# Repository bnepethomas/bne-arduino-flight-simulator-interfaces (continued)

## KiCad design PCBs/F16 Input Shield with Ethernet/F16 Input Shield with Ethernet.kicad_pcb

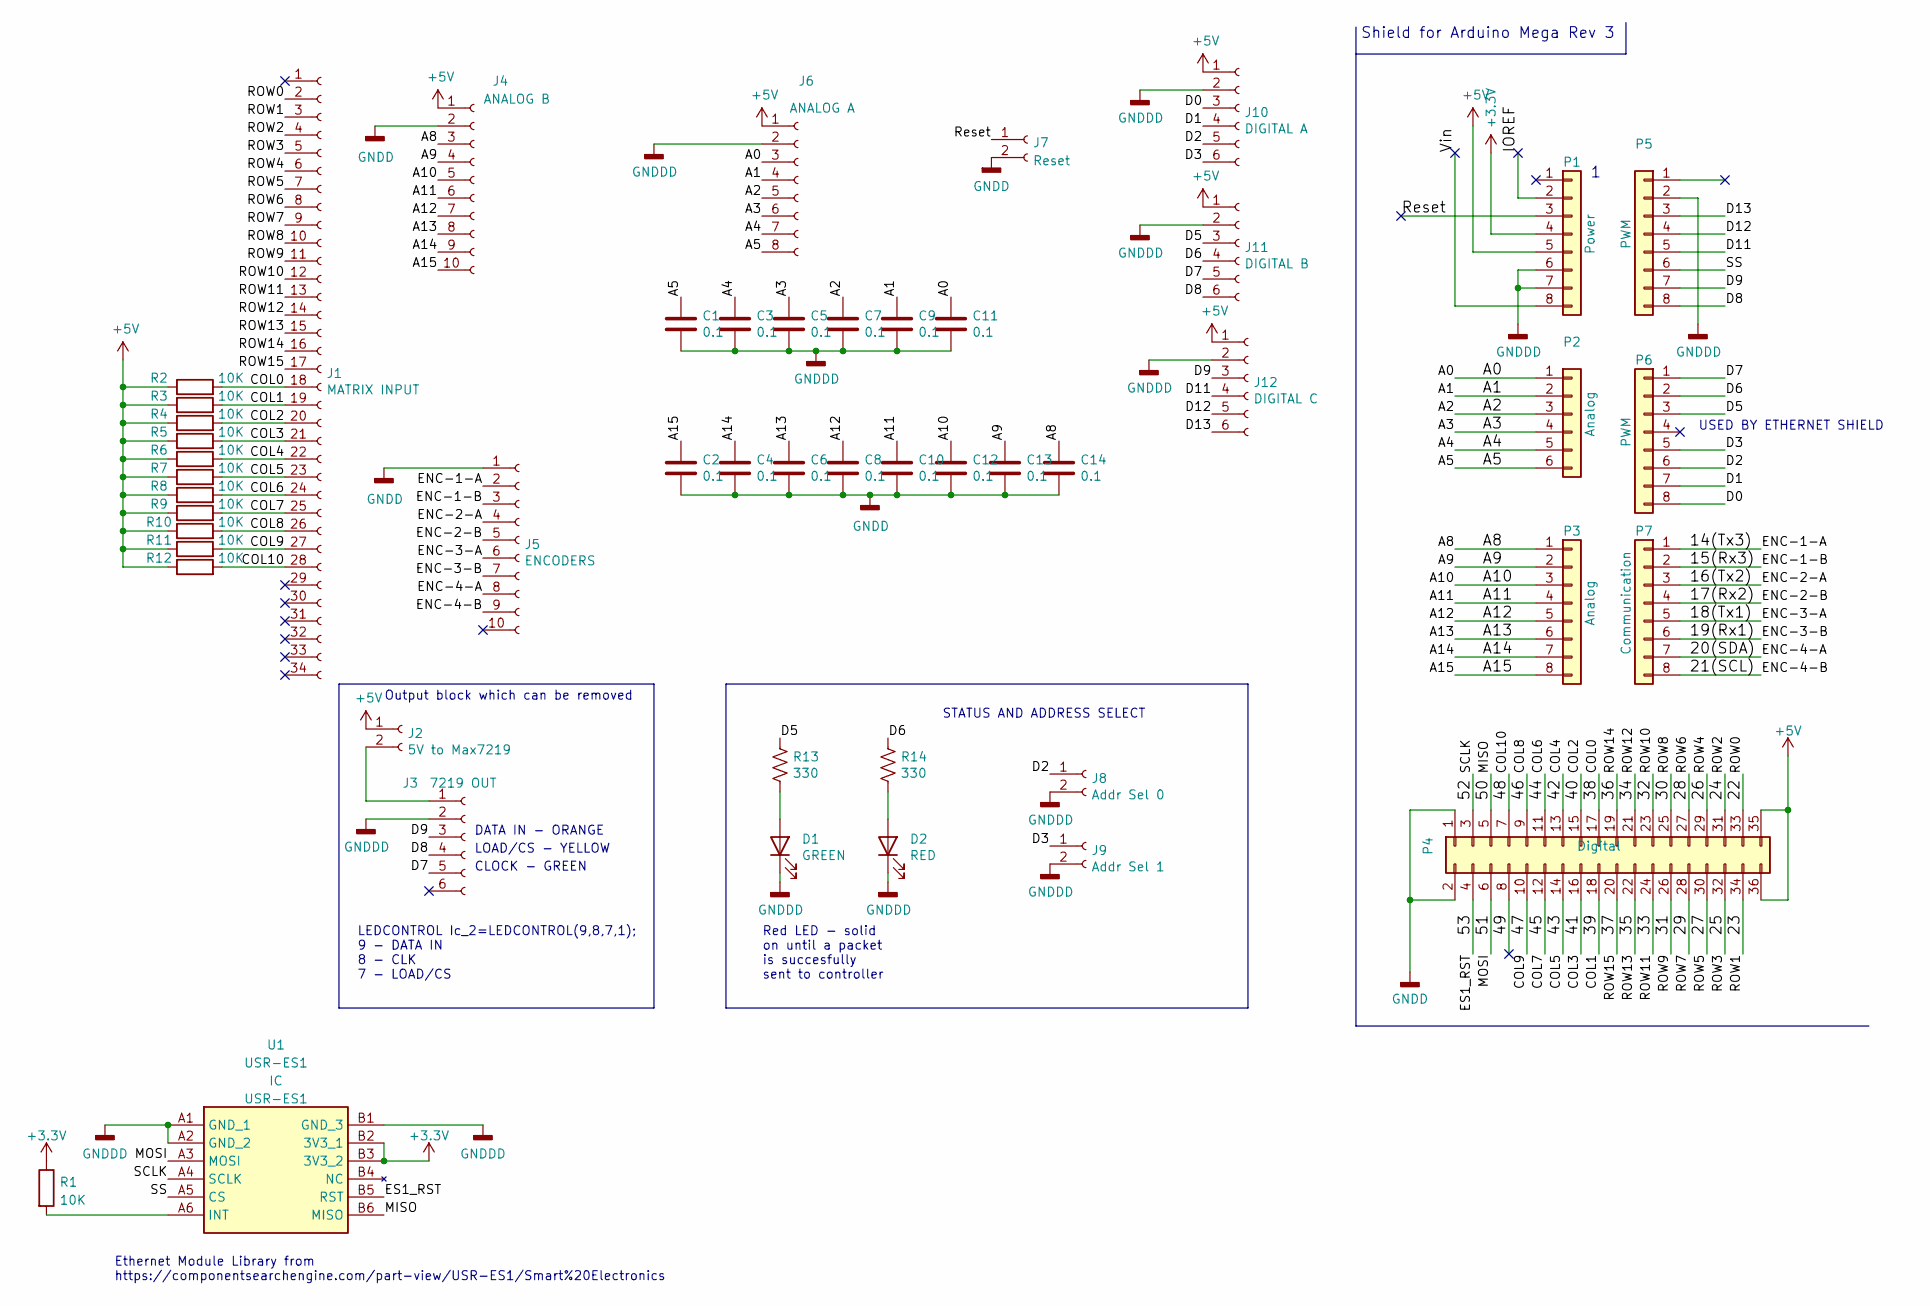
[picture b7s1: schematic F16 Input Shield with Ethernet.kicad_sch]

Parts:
C1, C2, C3, C4, C5, C6, C7, C8, C9, C10, C11, C12, C13, C14: 0.1; C_Disc_D6.0mm_W2.5mm_P5.00mm
D1: GREEN; LED_D3.0mm
D2: RED; LED_D3.0mm
J1: MATRIX INPUT; IDC-Header_2x17_P2.54mm_Vertical
J2: 5V to Max7219; Molex_1x02_P2.54mm_Vertical
J3: 7219 OUT; Molex_1x06_P2.54mm_Vertical
J4: ANALOG B; Molex_1x10_P2.54mm_Vertical
J5: ENCODERS; Molex_1x10_P2.54mm_Vertical
J6: ANALOG A; Molex_1x08_P2.54mm_Vertical
J7: Reset; PinHeader_1x02_P2.54mm_Vertical
J8: Addr Sel 0; PinHeader_1x02_P2.54mm_Vertical
J9: Addr Sel 1; PinHeader_1x02_P2.54mm_Vertical
J10: DIGITAL A; Molex_1x06_P2.54mm_Vertical
J11: DIGITAL B; Molex_1x06_P2.54mm_Vertical
J12: DIGITAL C; Molex_1x06_P2.54mm_Vertical
P1: Power; Socket_Strip_Arduino_1x08
P2: Analog; PinHeader_1x06_P2.54mm_Vertical
P3: Analog; Socket_Strip_Arduino_1x08
P4: Digital; Socket_Strip_Arduino_2x18
P5, P6: PWM; Socket_Strip_Arduino_1x08
P7: Communication; Socket_Strip_Arduino_1x08
R1, R2, R3, R4, R5, R6, R7, R8, R9, R10, R11, R12: 10K; PT_R_Axial_DIN0204_L3.6mm_D1.6mm_P2.54mm_Vertical
R13, R14: 330; PT_R_Axial_DIN0204_L3.6mm_D1.6mm_P2.54mm_Vertical
U1: USR-ES1; USRES1; Manufacturer_Part_Number USR-ES1

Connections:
+5V: J2.1, J4.1, J6.1, J10.1, J11.1, J12.1, P1.5, P4.35, P4.36, R2.1, R3.1, R4.1, R5.1, R6.1, R7.1, R8.1, R9.1, R10.1, R11.1, R12.1
/14(Tx3): J5.2, P7.1
/15(Rx3): J5.3, P7.2
/16(Tx2): J5.4, P7.3
/17(Rx2): J5.5, P7.4
/18(Tx1): J5.6, P7.5
/19(Rx1): J5.7, P7.6
/20(SDA): J5.8, P7.7
/21(SCL): J5.9, P7.8
/22: J1.2, P4.33
/23: J1.3, P4.34
/24: J1.4, P4.31
/25: J1.5, P4.32
/26: J1.6, P4.29
/27: J1.7, P4.30
/28: J1.8, P4.27
/29: J1.9, P4.28
/30: J1.10, P4.25
/31: J1.11, P4.26
/32: J1.12, P4.23
/33: J1.13, P4.24
/34: J1.14, P4.21
/35: J1.15, P4.22
/36: J1.16, P4.19
/37: J1.17, P4.20
/38: J1.18, P4.17, R2.2
/39: J1.19, P4.18, R3.2
/40: J1.20, P4.15, R4.2
/41: J1.21, P4.16, R5.2
/42: J1.22, P4.13, R6.2
/43: J1.23, P4.14, R7.2
/44: J1.24, P4.11, R8.2
/45: J1.25, P4.12, R9.2
/46: J1.26, P4.9, R10.2
/47: J1.27, P4.10, R11.2
/48: J1.28, P4.7, R12.2
/49: P4.8
/50: P4.5, U1.B6 (MISO)
/51: P4.6, U1.A3 (MOSI)
/52: P4.3, U1.A4 (SCLK)
/53: P4.4, U1.B5 (RST)
/A0: C11.1, J6.3, P2.1
/A1: C9.1, J6.4, P2.2
/A2: C7.1, J6.5, P2.3
/A3: C5.1, J6.6, P2.4
/A4: C3.1, J6.7, P2.5
/A5: C1.1, J6.8, P2.6
/A8: C14.1, J4.3, P3.1
/A9: C13.1, J4.4, P3.2
/A10: C12.1, J4.5, P3.3
/A11: C10.1, J4.6, P3.4
/A12: C8.1, J4.7, P3.5
/A13: C6.1, J4.8, P3.6
/A14: C4.1, J4.9, P3.7
/A15: C2.1, J4.10, P3.8
/D0: J10.3, P6.8
/D1: J10.4, P6.7
/D2: J8.1, J10.5, P6.6
/D3: J9.1, J10.6, P6.5
/D5: J11.3, P6.3, R13.1
/D6: J11.4, P6.2, R14.1
/D7: J3.5, J11.5, P6.1
/D8: J3.4, J11.6, P5.8
/D9: J3.3, J12.3, P5.7
/D11: J12.4, P5.5
/D12: J12.5, P5.4
/D13: J12.6, P5.3
/IOREF: P1.2
/Reset: J7.1, P1.3
/SS: P5.6, U1.A5 (CS)
/Vin: P1.8
unnamed: D1.2 (A), R13.2
unnamed: D2.2 (A), R14.2
unnamed: J2.2, J3.1
unnamed: R1.2, U1.A6 (INT)

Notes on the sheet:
LEDCONTROL Ic_2=LEDCONTROL(9,8,7,1); 9 - DATA IN 8 - CLK 7 - LOAD/CS
Ethernet Module Library from https://componentsearchengine.com/part-view/USR-ES1/Smart%20Electronics
Shield for Arduino Mega Rev 3
Red LED - solid on until a packet is succesfully sent to controller
LOAD/CS - YELLOW
DATA IN - ORANGE
Output block which can be removed
CLOCK - GREEN
USED BY ETHERNET SHIELD
STATUS AND ADDRESS SELECT

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
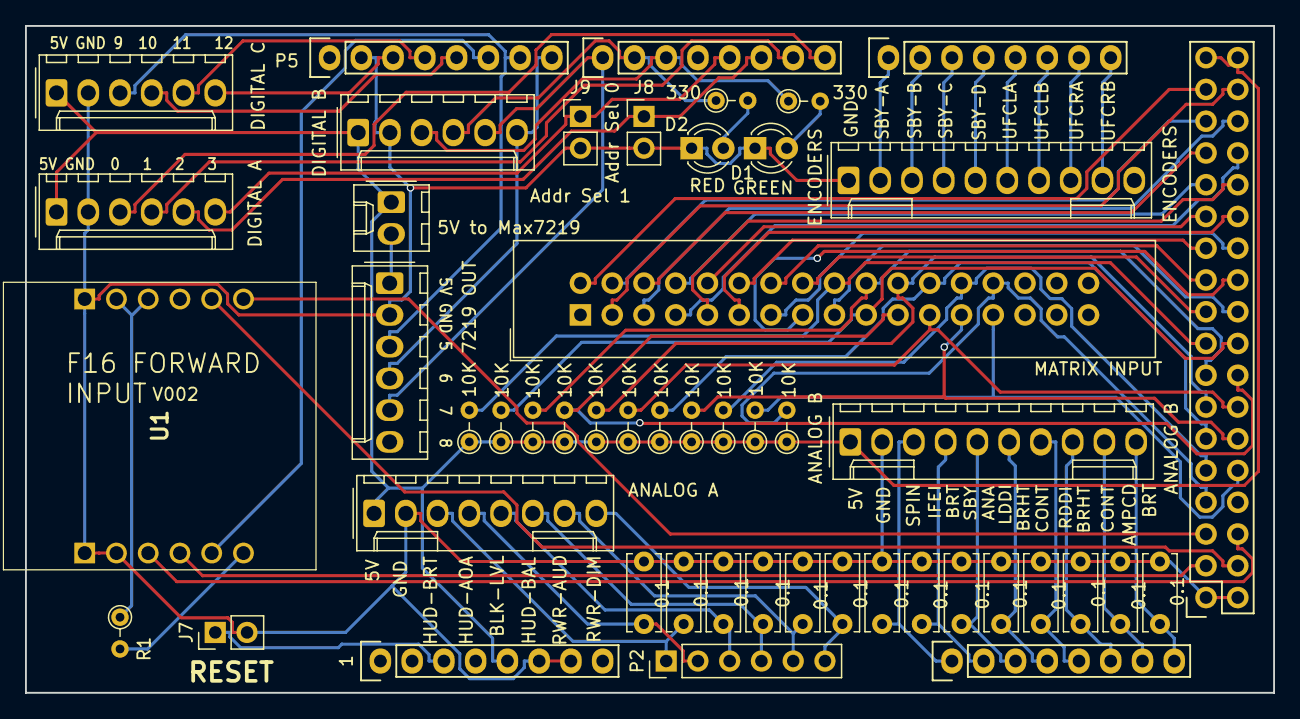
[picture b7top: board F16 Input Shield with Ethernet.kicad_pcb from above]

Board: 2 copper layers, 99.8 x 53.3 mm, 50 parts (0 on the bottom side), 74 nets.
